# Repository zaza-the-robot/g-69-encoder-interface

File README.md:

# g-69-encoder-interface
Interfaces an HEDS-5000 series encoder to a HEDS-9000 interface

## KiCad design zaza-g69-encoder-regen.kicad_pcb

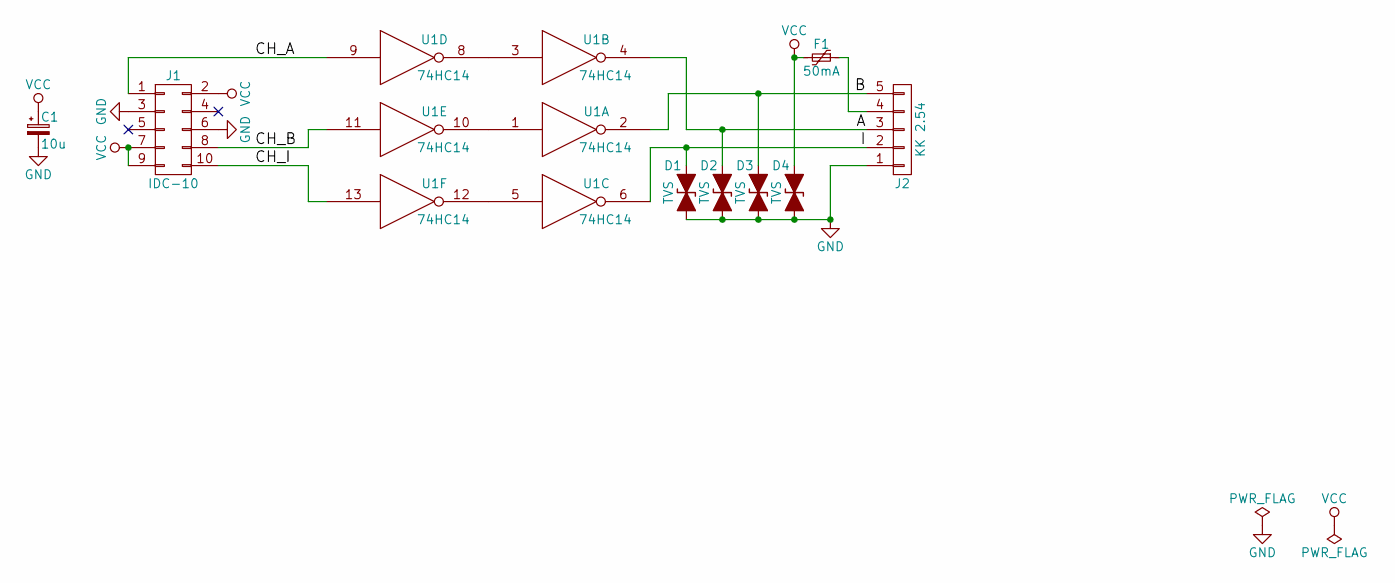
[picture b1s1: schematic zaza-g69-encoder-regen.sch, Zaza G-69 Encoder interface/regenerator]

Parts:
C1: 10u; CP_Tantalum_Case-X_EIA-7343-43_Reflow
D1, D2, D3, D4: TVS; D_SOD-323
F1: 50mA; R_1206
J1: IDC-10; Pin_Header_Angled_2x05_Pitch2.54mm
J2: KK 2.54; Molex_KK-6410-05_05x2.54mm_Straight
U1: 74HC14; SOIC-14_3.9x8.7mm_Pitch1.27mm

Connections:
/A: D2.1 (A1), J2.3, U1.4
/B: D3.1 (A1), J2.5, U1.2
/CH_A: J1.1, U1.9
/CH_B: J1.8, U1.11
/CH_I: J1.10, U1.13
/I: D1.1 (A1), J2.2, U1.6
GND: C1.2, D1.2 (A2), D2.2 (A2), D3.2 (A2), D4.2 (A2), J1.3, J1.6, J2.1, U1.7 (GND)
unnamed: F1.1, J2.4
unnamed: U1.1, U1.10
unnamed: U1.3, U1.8
unnamed: U1.5, U1.12
VCC: C1.1, D4.1 (A1), F1.2, J1.2, J1.7, J1.9, U1.14 (VCC)

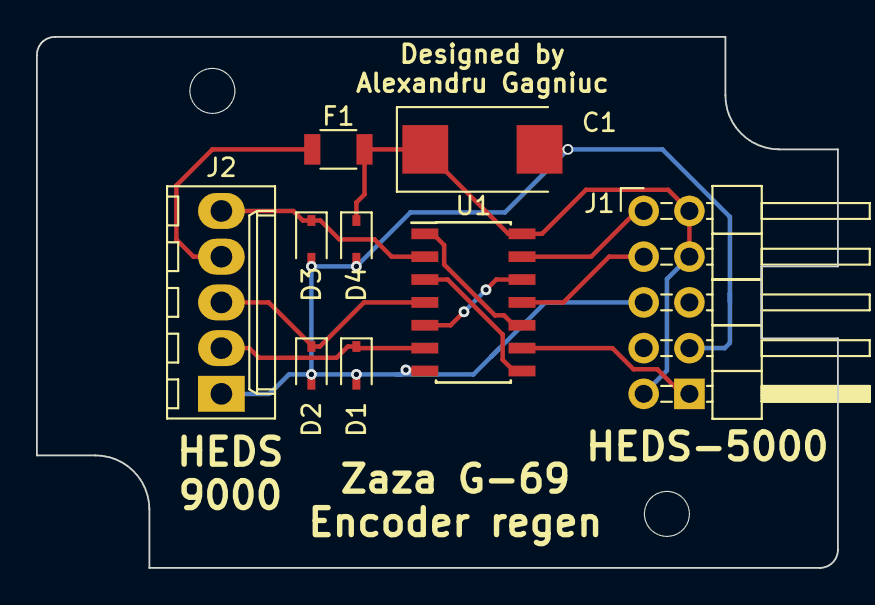
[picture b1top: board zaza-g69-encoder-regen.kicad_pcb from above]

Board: 2 copper layers, 44.5 x 29.5 mm, 9 parts (0 on the bottom side), 12 nets.

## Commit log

2017-11-05 Add schematic and layout for Rev0
    This is designed to fit in a hammond 1551F (1551FBK or 1551FGY) case,
    with additional machining. There are two versions:
    standard: HEDS-5000 connector mounted through-hole.
    -smd: HEDS-5000 connector edge-mounted, surface mount.
    While both of these will fit in the Hammond case, the -smd version may
    incurr lower machining costs, as it does not involve modifications to
